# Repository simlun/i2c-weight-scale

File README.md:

I²C Weight Scale
================

_I²C Weight Scale: strain gauges in a Wheatstone bridge amplified in an
instrumentation amplifier, A/D converted and made available over I²C in a PIC
microcontroller._

I²C slave. Reading from the slave responds with a stable digital representation
of the load on the strain gauges under a hacked ordinary weight scale.

Schematic
---------

The [KiCad](http://www.kicad.org/) source files can be found under `PCB/`.
The schematic rendered as a PDF is reached by clicking the PNG below.. The
KiCad project depends on [my component library](https://github.com/simlun/kicad-library-by-simlun)
which should be checked out alongside this repository.

Hacked Weight Scale
-------------------

Simply buy a cheap kitchen weight scale, remove its PCB and instead take the
4x3=12 leads from the 4 strain gauges to create an external port from a 2.54 mm
pin header.

The I²C Weight Scale PCB is a module that can connect to any weight scale of 4
strain gauges.

License
-------

This work is licensed under the Creative Commons Attribution-ShareAlike 4.0
International License. To view a copy of this license, visit
http://creativecommons.org/licenses/by-sa/4.0/ or send a letter to Creative
Commons, PO Box 1866, Mountain View, CA 94042, USA.

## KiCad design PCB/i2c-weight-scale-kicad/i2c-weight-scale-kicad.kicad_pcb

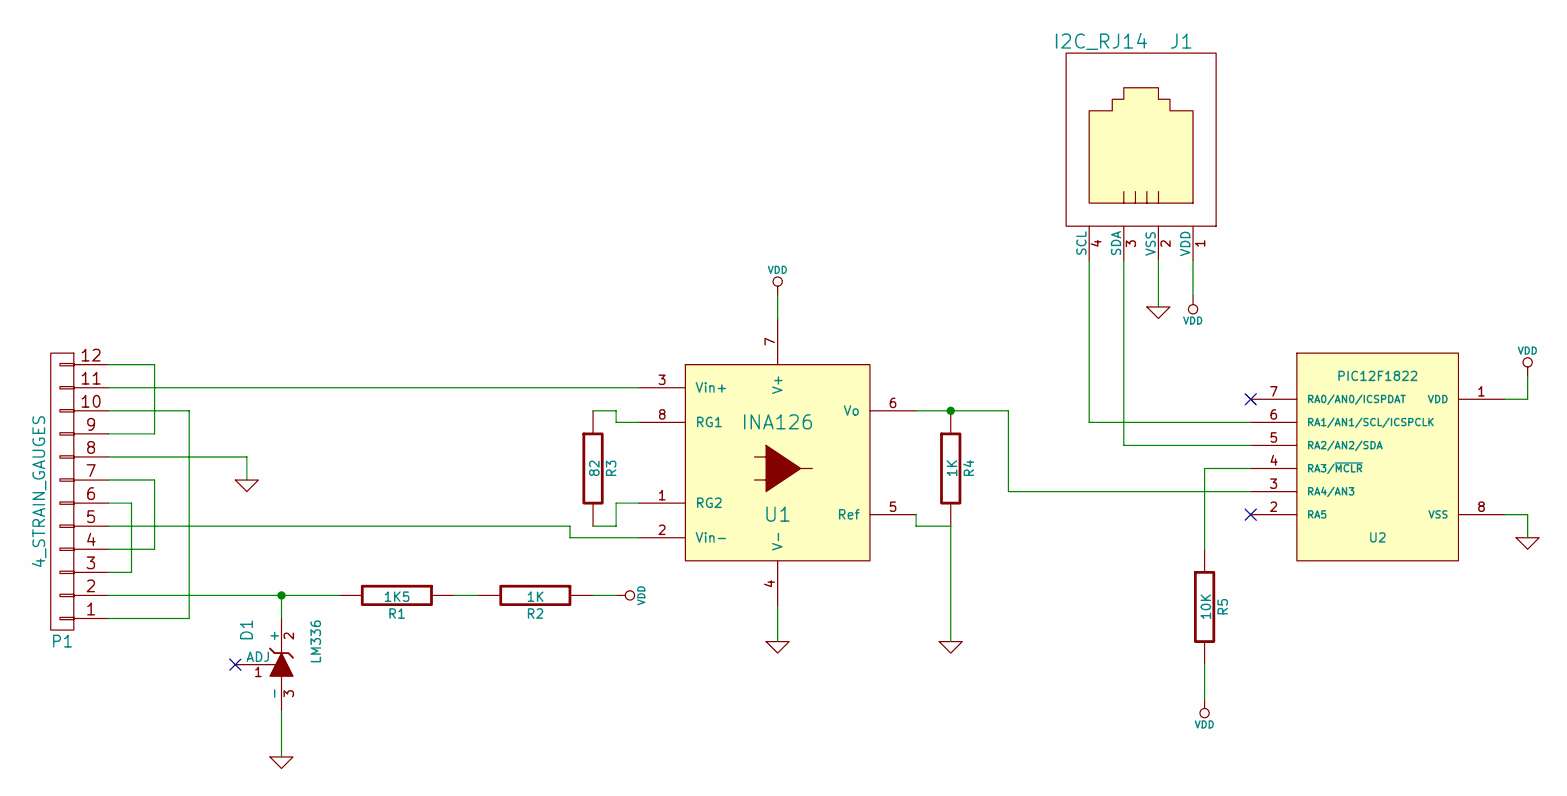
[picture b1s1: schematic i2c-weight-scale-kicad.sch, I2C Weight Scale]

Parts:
D1: LM336; TO-92-Free-molded-wide-oval
J1: I2C_RJ14; RJ14_6P4C_right_angle_Molex_95009-7641
P1: 4_STRAIN_GAUGES; Pin_Header_Straight_1x12
R1: 1K5; Resistor_Vertical_RM5mm
R2, R4: 1K; Resistor_Vertical_RM5mm
R3: 82; Resistor_Vertical_RM5mm
R5: 10K; Resistor_Vertical_RM5mm
U1: INA126; DIP-8__300
U2: PIC12F1822; DIP-8__300

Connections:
GND: D1.3 (-), J1.2 (VSS), P1.8, R4.2, U1.4 (V-), U1.5 (Ref), U2.8 (VSS)
unnamed: D1.2 (+), P1.2, R1.2
unnamed: J1.3 (SDA), U2.5 (RA2/AN2/SDA)
unnamed: J1.4 (SCL), U2.6 (RA1/AN1/SCL/ICSPCLK)
unnamed: P1.1, P1.10
unnamed: P1.3, P1.6
unnamed: P1.4, P1.7
unnamed: P1.5, U1.2 (Vin-)
unnamed: P1.11, U1.3 (Vin+)
unnamed: P1.9, P1.12
unnamed: R1.1, R2.2
unnamed: R3.1, U1.8 (RG1)
unnamed: R3.2, U1.1 (RG2)
unnamed: R4.1, U1.6 (Vo), U2.3 (RA4/AN3)
unnamed: R5.1, U2.4 (RA3/~MCLR)
VDD: J1.1 (VDD), R2.1, R5.2, U1.7 (V+), U2.1 (VDD)

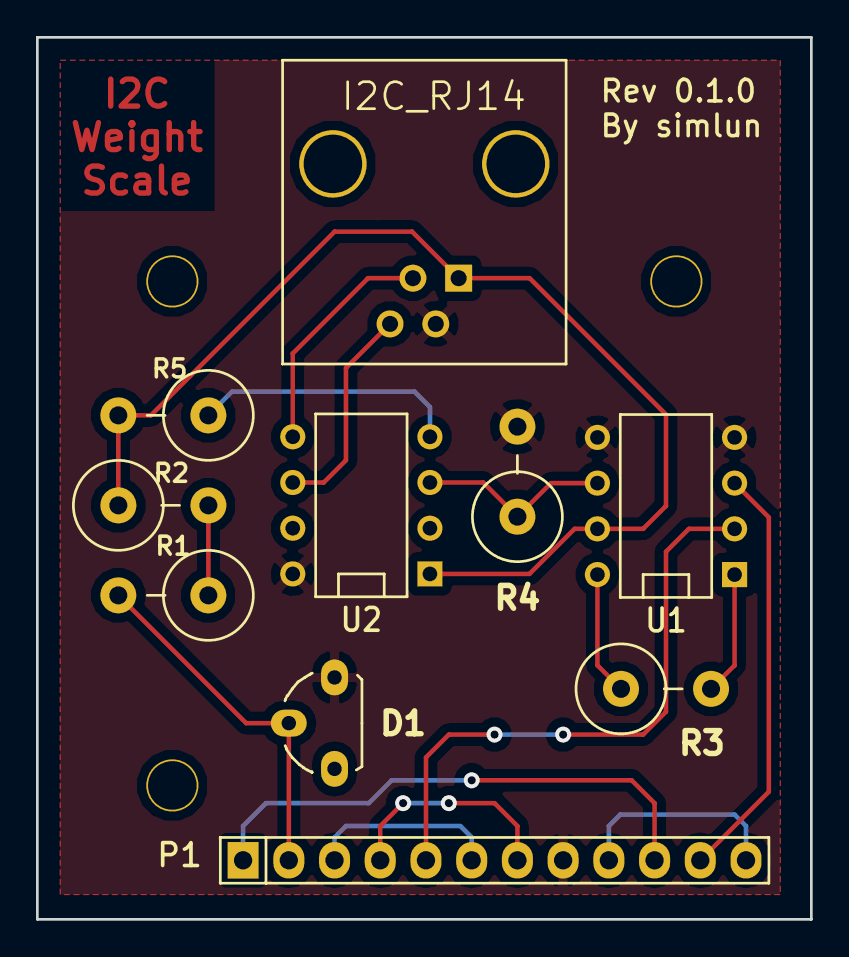
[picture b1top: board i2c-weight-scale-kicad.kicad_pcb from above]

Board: 2 copper layers, 43.0 x 49.0 mm, 13 parts (0 on the bottom side), 16 nets.

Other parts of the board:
MountingHole_2-7mm, MountingHole_2-7mm#2, MountingHole_2-7mm#3: VAL**; MountingHole_2-7mm

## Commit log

2014-11-03 Add Bill Of Materials documentation
2014-11-03 Hello, world (blinking LED on pin 2)
2014-11-03 Configure internal oscillator
2014-11-03 Refactor
2014-11-04 Add readme stub
2014-11-05 WIP: Started implementing an I2C slave
    - Currently an Electric Imp I2C master can successfully read one byte!
2014-11-08 Read 16 bits over I2C in two 8-bit I2C reads from a master
2014-11-08 Read 2 bytes over I2C in a single 2-byte I2C read from a master
2014-11-09 Refactoring and improved I2C implementation
2014-11-09 Refactor: modularize all the things
2014-11-09 Fix compilation warning
    - "illegal conversion between pointer types"
2014-11-11 Implement analog/digital conversion on pin 3
    - And let the I2C master read this 10 bit value!
    - Next up: decrease the impact of input noise by implementing some kind
    of moving average.
2014-11-12 Tweak the voltage reference and implement moving average
    - Next step: moving mean instead
2014-11-30 WIP: Start working on a PCB layout
2014-12-04 Complete the load cell and amplification schematic
2014-12-04 Add RJ14 and PIC12F1822 components
2014-12-06 Tweak electrical type to pass the electrical rule check
2014-12-06 Clean up power pins, use VDD instead of +5V
2014-12-06 Generate netlist
2014-12-06 Assign footprint to the LM336
2014-12-06 Assign footprints to resistors and ICs
2014-12-06 Associate last component with a custom footprint
2014-12-07 Add RJ14 connector and enclosure to BOM
2014-12-07 Add license information
2014-12-07 Add all footprints and draw PCB edge cuts
2014-12-07 Add mounting holes
2014-12-07 Rough footprint placements on the PCB
2014-12-08 Place the RJ14 connector on the PCB
2014-12-08 Move origins to upper left corner of PCB
2014-12-08 RJ14: Account for a PCB edge setback of 1.27 mm
2014-12-08 General PCB component placements
2014-12-08 Smarter resistor placement
2014-12-08 Strain gauge connector traces done
2014-12-09 Connect all nets and GND copper fill top and bottom
2014-12-13 Remove mechanical holes
2014-12-13 Create new mounting holes
2014-12-14 Add text
2014-12-14 Version 0.1.0 ready for fab
2014-12-29 Add schematic PDF to version 0.1.0
2015-05-03 Add pictures to the README
2015-05-03 Spelling
2015-05-03 Fix link
2015-05-03 Fix image paths
2021-11-10 Update README.md
    https://forum.kicad.info/t/warning-avoid-all-links-to-kicad-pcb-org-use-kicad-org/31521
